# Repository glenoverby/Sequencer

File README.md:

# Sequencer
An Arduino sequencer for amateur radio

This is an Arduino project used for sequencing transmit / receive relays,
amplifiers and transverters in order to prevent transmitting into a relay when
it is switching, and to protect recevier inputs from transmitters or amplifiers.

I've written [a full description of othe project.](sequencer.md)

The source code is in this repository under Software and the KiCad files
for a PCB are under Hardware/sequencer3. I had this board manufactured by
OshPark in 2024.

# Arduino Clone (sort of)

I wanted to reduce the cost of this project, and the MegaAVR chip itself is
about a tenth of the price of an Arduino board. I can get by with just the
AVR and a few support chips. I made an arduino style board for the ATMega328
in a TQFP package.

[Find it here](Hardware/Mega328basic1)

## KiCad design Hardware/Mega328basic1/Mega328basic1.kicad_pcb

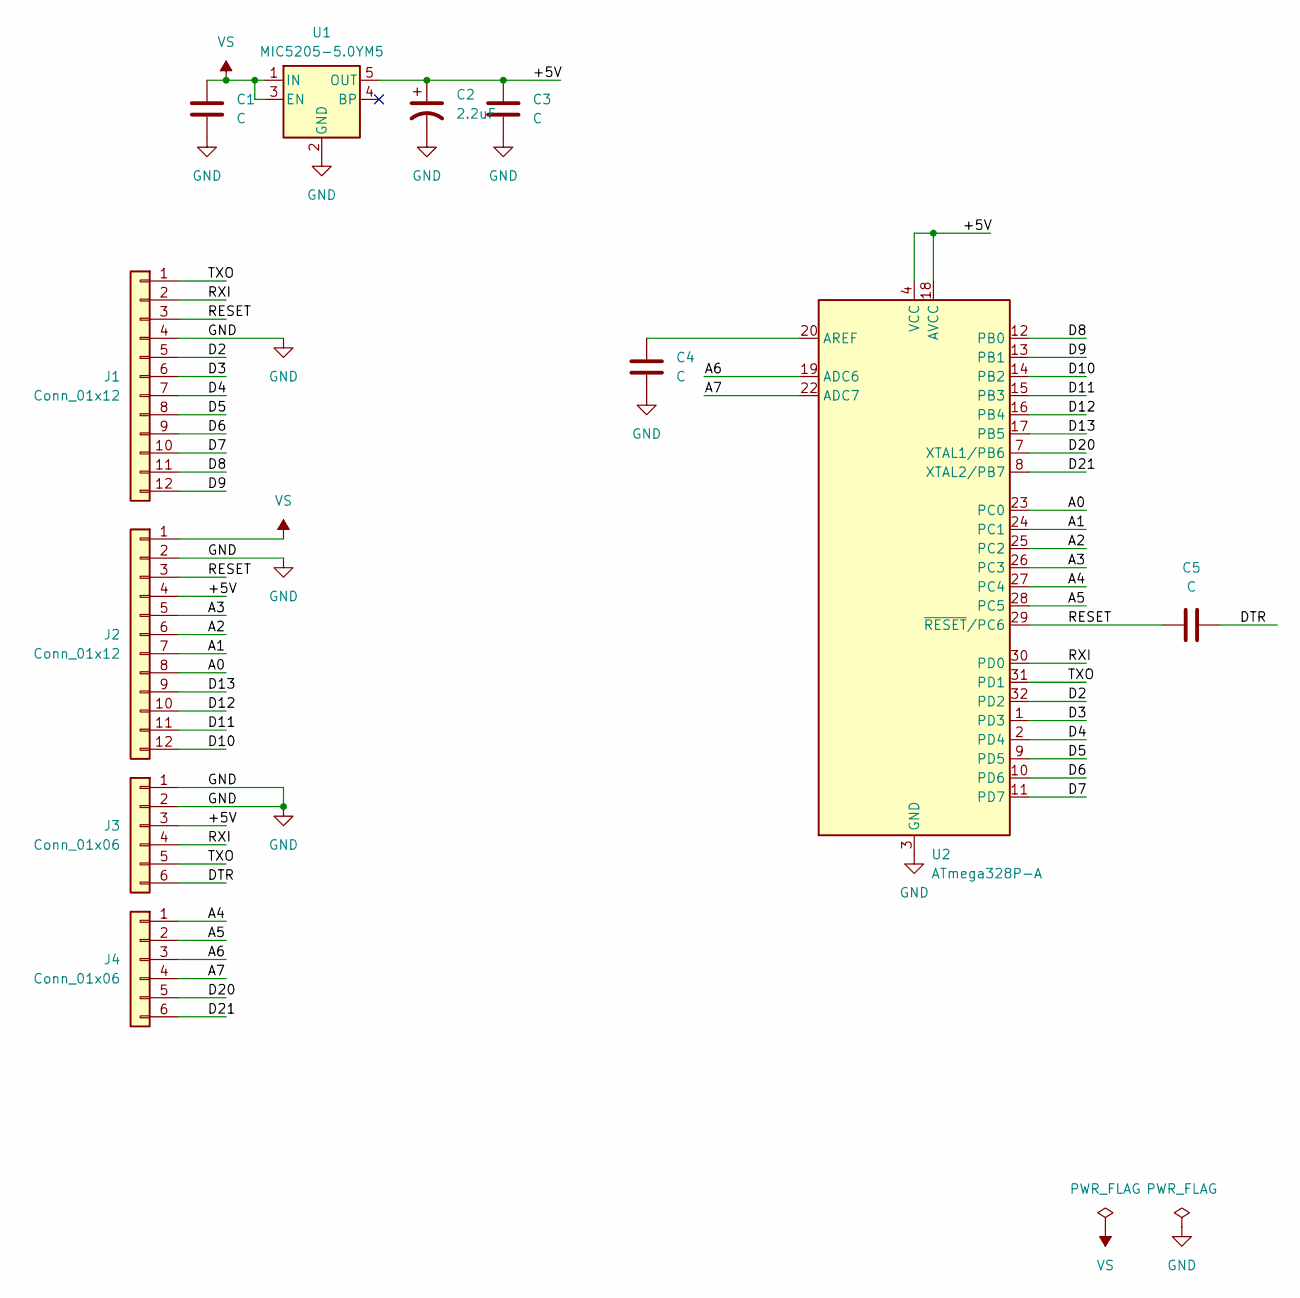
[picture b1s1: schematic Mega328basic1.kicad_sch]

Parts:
C1, C3, C4, C5: C; C_0805_2012Metric_Pad1.18x1.45mm_HandSolder
C2: 2.2uF; C_0805_2012Metric_Pad1.18x1.45mm_HandSolder
J1, J2: Conn_01x12; PinSocket_1x12_P2.54mm_Vertical
J3, J4: Conn_01x06; PinSocket_1x06_P2.54mm_Vertical
U1: MIC5205-5.0YM5; SOT-23-5
U2: ATmega328P-A; TQFP-32_7x7mm_P0.8mm

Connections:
/+5V: C2.1, C3.1, J2.4, J3.3, U1.5 (OUT), U2.4 (VCC), U2.6 (VCC), U2.18 (AVCC)
/A0: J2.8, U2.23 (PC0)
/A1: J2.7, U2.24 (PC1)
/A2: J2.6, U2.25 (PC2)
/A3: J2.5, U2.26 (PC3)
/A4: J4.1, U2.27 (PC4)
/A5: J4.2, U2.28 (PC5)
/A6: J4.3, U2.19 (ADC6)
/A7: J4.4, U2.22 (ADC7)
/D2: J1.5, U2.32 (PD2)
/D3: J1.6, U2.1 (PD3)
/D4: J1.7, U2.2 (PD4)
/D5: J1.8, U2.9 (PD5)
/D6: J1.9, U2.10 (PD6)
/D7: J1.10, U2.11 (PD7)
/D8: J1.11, U2.12 (PB0)
/D9: J1.12, U2.13 (PB1)
/D10: J2.12, U2.14 (PB2)
/D11: J2.11, U2.15 (PB3)
/D12: J2.10, U2.16 (PB4)
/D13: J2.9, U2.17 (PB5)
/D20: J4.5, U2.7 (XTAL1/PB6)
/D21: J4.6, U2.8 (XTAL2/PB7)
/DTR: C5.2, J3.6
/RESET: C5.1, J1.3, J2.3, U2.29 (~RESET/PC6)
/RXI: J1.2, J3.4, U2.30 (PD0)
/TXO: J1.1, J3.5, U2.31 (PD1)
GND: C1.2, C2.2, C3.2, C4.2, J1.4, J2.2, J3.1, J3.2, U1.2 (GND), U2.3 (GND), U2.5 (GND), U2.21 (GND)
unnamed: C4.1, U2.20 (AREF)
VS: C1.1, J2.1, U1.1 (IN), U1.3 (EN)

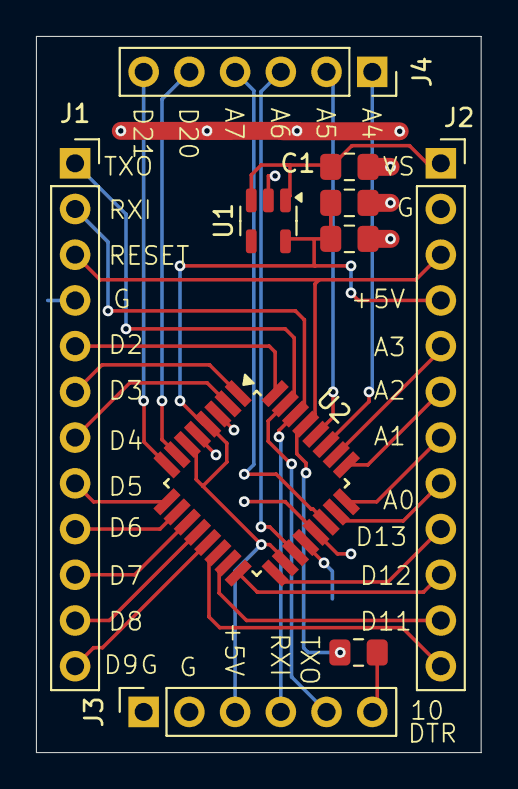
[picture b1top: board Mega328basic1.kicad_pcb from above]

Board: 2 copper layers, 24.7 x 39.8 mm, 11 parts (1 on the bottom side), 30 nets.

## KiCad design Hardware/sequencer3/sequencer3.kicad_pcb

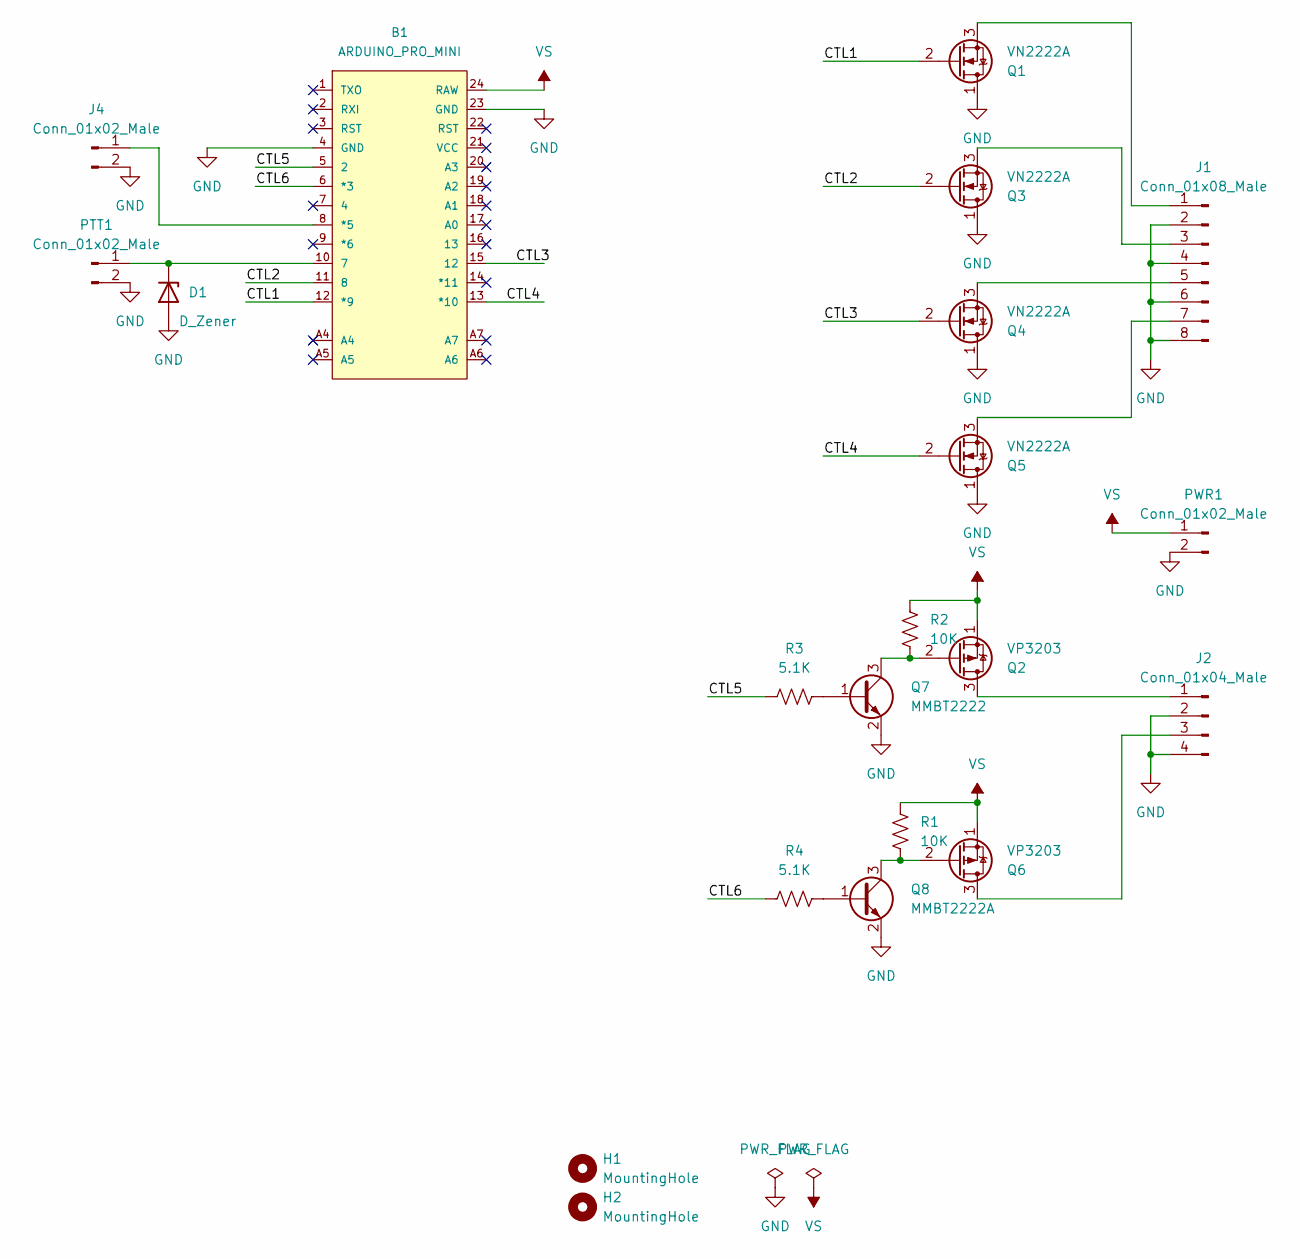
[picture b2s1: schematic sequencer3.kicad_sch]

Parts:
B1: ARDUINO_PRO_MINI
D1: D_Zener; D_DO-34_SOD68_P5.08mm_Vertical_KathodeUp
H1, H2: MountingHole; MountingHole_3.2mm_M3
J1: Conn_01x08_Male; PinHeader_2x04_P2.54mm_Vertical
J2: Conn_01x04_Male; PinHeader_2x02_P2.54mm_Vertical
J4: Conn_01x02_Male; PinHeader_1x02_P2.54mm_Vertical
PTT1: Conn_01x02_Male; PinHeader_1x02_P2.54mm_Vertical
PWR1: Conn_01x02_Male; PinHeader_1x02_P2.54mm_Vertical
Q1, Q3, Q4, Q5: VN2222A; TO-92_Inline
Q2, Q6: VP3203; TO-92_Inline
Q7: MMBT2222; SOT-23
Q8: MMBT2222A; SOT-23
R1, R2: 10K; R_0805_2012Metric_Pad1.20x1.40mm_HandSolder
R3, R4: 5.1K; R_0805_2012Metric_Pad1.20x1.40mm_HandSolder

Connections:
/CTL1: B1.12 (*9), Q1.2 (G)
/CTL2: B1.11 (8), Q3.2 (G)
/CTL3: B1.15 (12), Q4.2 (G)
/CTL4: B1.13 (*10), Q5.2 (G)
/CTL5: B1.5 (2), R3.2
/CTL6: B1.6 (*3), R4.2
GND: B1.4 (GND), B1.23 (GND), D1.2 (A), J1.2, J1.4, J1.6, J1.8, J2.2, J2.4, J4.2, PTT1.2, PWR1.2, Q1.1 (D), Q3.1 (D), Q4.1 (D), Q5.1 (D), Q7.2 (E), Q8.2 (E)
unnamed: B1.10 (7), D1.1 (K), PTT1.1
unnamed: B1.8 (*5), J4.1
unnamed: J1.1, Q1.3 (S)
unnamed: J1.3, Q3.3 (S)
unnamed: J1.5, Q4.3 (S)
unnamed: J1.7, Q5.3 (S)
unnamed: J2.1, Q2.3 (D)
unnamed: J2.3, Q6.3 (D)
unnamed: Q2.2 (G), Q7.3 (C), R2.2
unnamed: Q6.2 (G), Q8.3 (C), R1.2
unnamed: Q7.1 (B), R3.1
unnamed: Q8.1 (B), R4.1
VS: B1.24 (RAW), PWR1.1, Q2.1 (S), Q6.1 (S), R1.1, R2.1

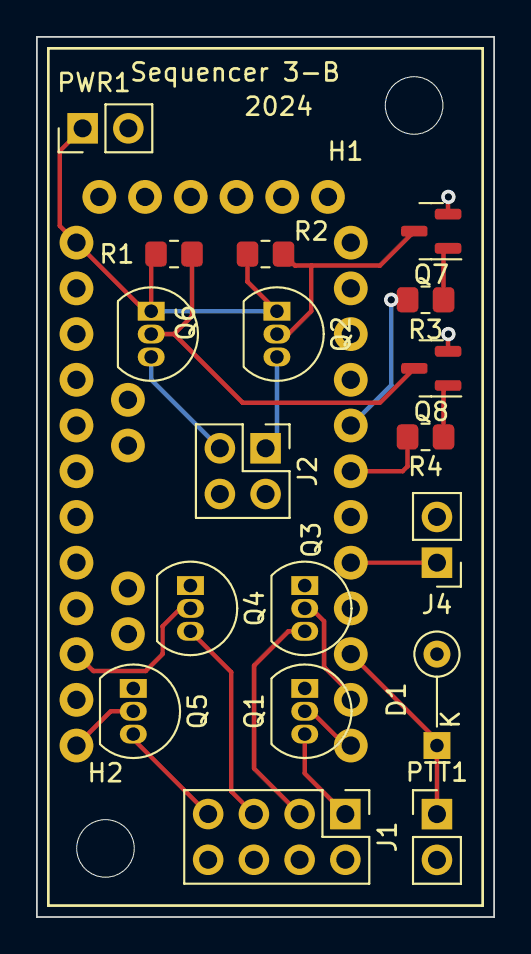
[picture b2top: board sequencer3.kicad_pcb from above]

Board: 2 copper layers, 25.4 x 48.9 mm, 21 parts (1 on the bottom side), 20 nets.

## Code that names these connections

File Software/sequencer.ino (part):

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 *
 * Arduino Mega328p
 *  CPU Arduino Function
 *  PD0 0       RX
 *  PD1 1       TX
 *  PD2 2       D2        1 - Low
 *  PD3 3       D3        2 - Low
 *  PD4 4       D4        3 - Low
 *  PD5 5       D5        4 - Low
 *  PD6 6       D6        5 - Low
 *  PD7 7       D7        6 - Low
 *  PB0 8       D8        1 - Pulse Low On
 *  PB1 9       D9        2 - Pulse Low On
 *  PB2 10      D10       1 - Pulse Low Off
 *  PB3 11      MOSI      2 - Pulse Low Off
 *  PB4 12      MISO      PTT-L Input
 *  PB5 13      SCK & LED
 *  PB6         Xtal 1
 *  PB7         Xtal 2
 *  PC0 14      A0        1 - High
 *  PC1 15      A1        2 - High
 *  PC2 16      A2        3 - High
 *  PC3 17      A3        4 - High
 *  PC4 18      A4        5 - High
 *  PC5 19      A5        6 - High
 *
 * AdaFruit ItsyBitsy Mega32u4
 *  ports A2 - A5 don't seem to function as outputs.
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

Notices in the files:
Software/sequencer.ino:
Copyright 2006, 2019, 2022-2023 Glen Overby, All Rights Reserved
